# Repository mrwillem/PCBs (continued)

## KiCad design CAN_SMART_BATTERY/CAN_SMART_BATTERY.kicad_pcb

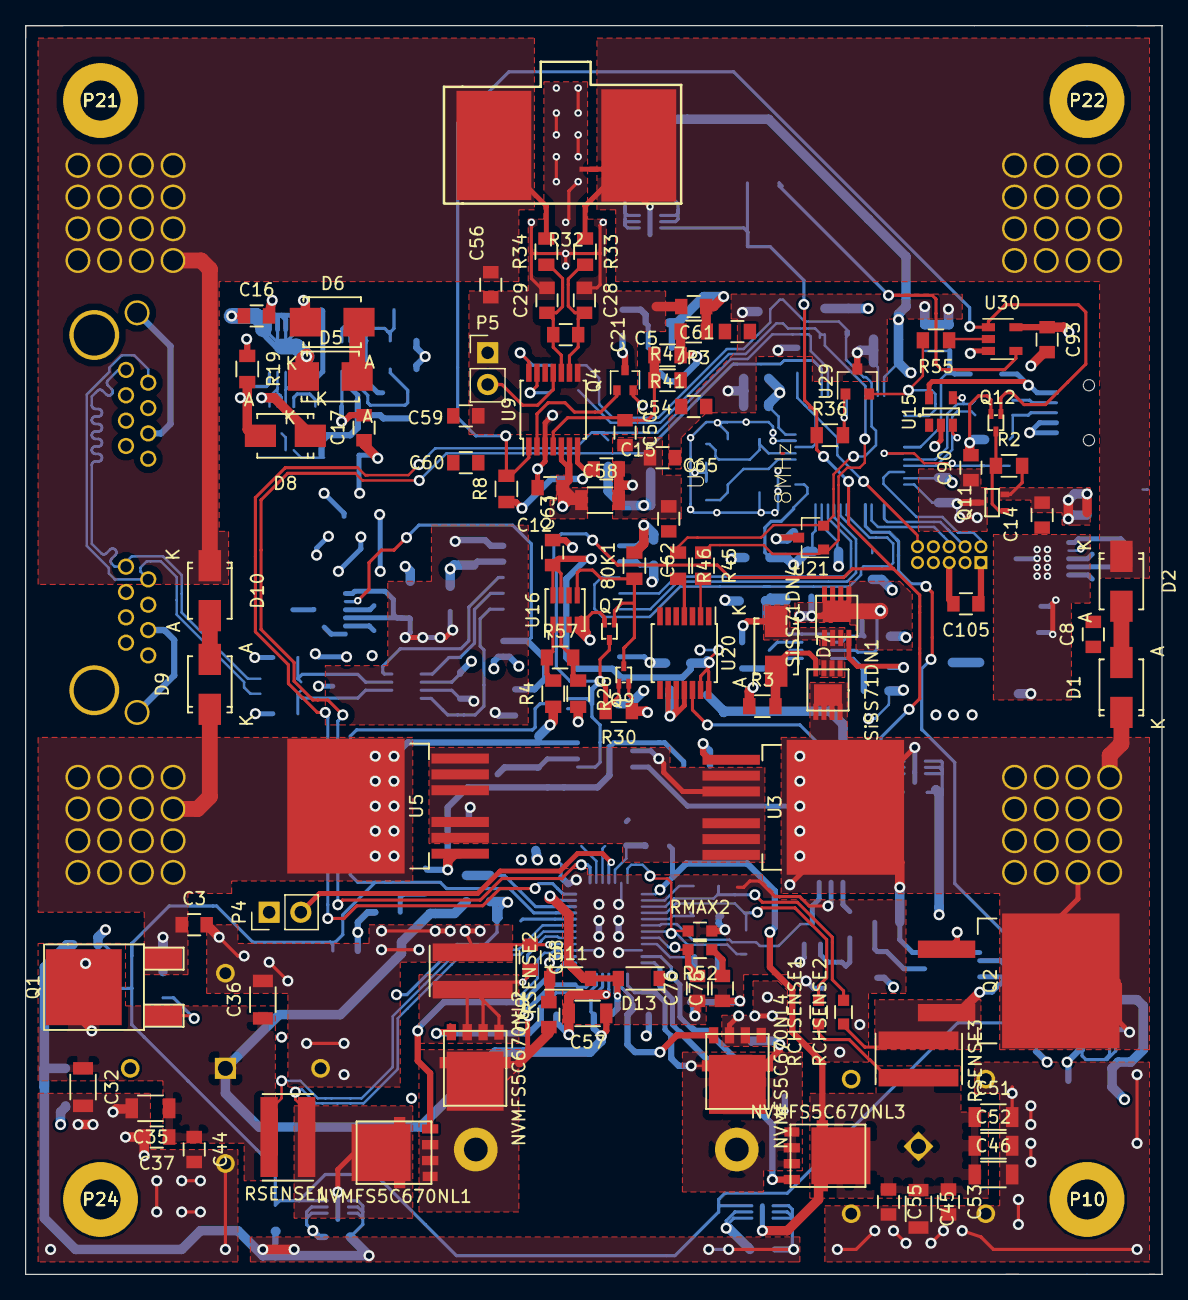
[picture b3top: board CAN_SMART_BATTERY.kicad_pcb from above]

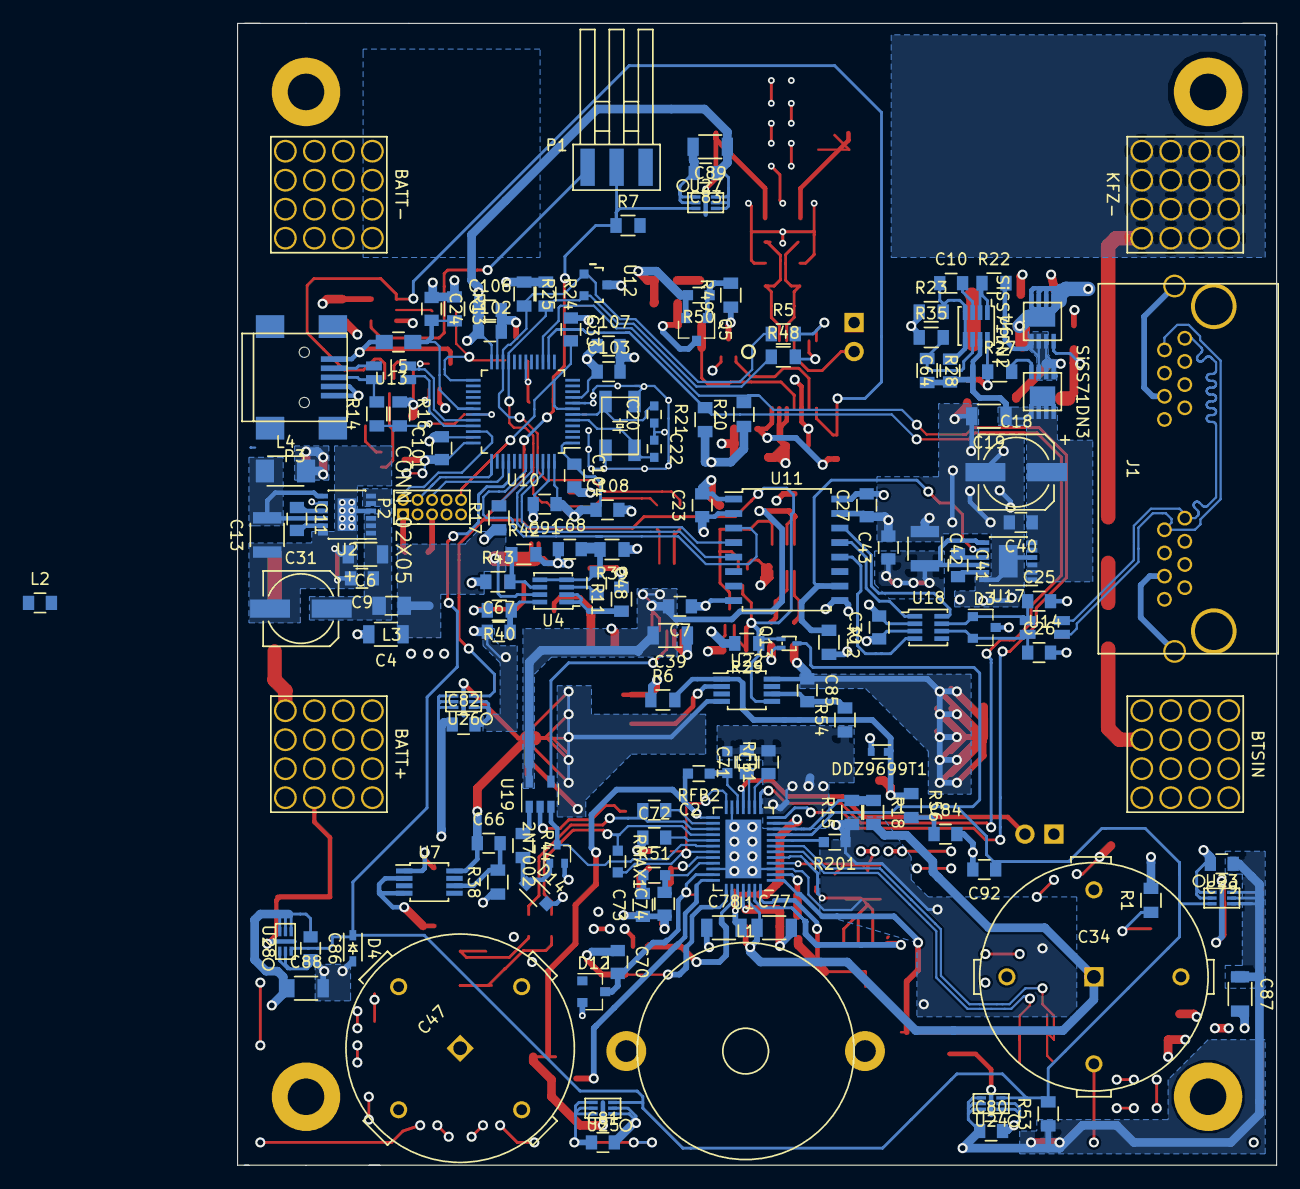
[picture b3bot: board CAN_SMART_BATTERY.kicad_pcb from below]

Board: 4 copper layers, 91.0 x 100.0 mm, 249 parts (144 on the bottom side), 134 nets.

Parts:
2N7002: Q_NMOS_GSD; SOT-323
80K1: R; R_0805_HandSolder
BATT+1: BATT+; WE_threaded_shank_M5_160A
BATT-1: BATT-; WE_threaded_shank_M5_160A
BTSIN1: BTSIN; WE_threaded_shank_M5_160A
C1, C64, C68: 470nF; C_0805
C2, C72: 100pF; C_0805
C3, C8: 100pF 150V; C_0805
C4, C6, C19, C32, C35, C36, C45, C46, C51, C52: 4.7uF GRM31CR71H47; C_1206
C5, C7, C9, C12, C21, C23, C24, C25, C26, C27, C28, C29, C30, C33, C37, C40, C44, C53, C54, C55, C56, C59, C60, C61, C62, C63, C65, C79, C80, C81, C82, C83, C86, C91, C93, C101, C102, C103, C104, C105: 100nF; C_0805
C10, C15, C48: 1uF; C_0805
C11, C41: 1uF 0805ZC105KAT2A; C_0805
C13, C42: 10uF; C_1210
C14, C43: 1uF GRM219R71E105KA88D; C_0805
C16: 100pF 60V; C_0805
C17, C67: 2nFC; C_0805
C18, C31: 33uF; c_elec_6.3x7.7
C20, C22: 22pF; C_0603
C34, C47: 56uF; Capacitors_PEH225MF_20mm
C38: 333nF; C_0805
C39, C57, C58, C78: 10uF; C_1206
C50: 3,3nF; C_0805
C66, C85: 47nF; C_0805
C69, C70, C73, C74, C75, C76: C; C_0805
C71: 220nF; C_0805
C77: 100nF; C_1206
C84, C92: 10nF; C_0805
C87, C88, C89: 4,7uF; C_1206
C90, C107: 4,7uF; C_0805
C106, C108: 2,2uF; C_0805
D1, D2, D7, D8, D9, D10: ZENER; SMA_Standard
D3: D_Schottky_x2_ACom_KKA; SOT-23
D4: ZENER; SOD-323-Handsoldering
D5, D6: ZENER; SMB_Standard
D11: D_Schottky; SOD-123
D12: D_Schottky_x2_KCom_AAK; SOT-23
D13: SBR0560S1; SOD-123
D14: ZENER; SOD-323_HandSoldering
DDZ9699T1: ZENER; SOD-523
J1: RJHSE-5380-02; RJHSE538X-02-noled
JP1: Jumper_NC_Small; NetTie-I_Connected_SMD
JP2: Jumper_NC_Small; NetTie0.4mmSMD
JP3: Jumper_NO_Small; R_0805_HandSolder
KFZ-1: KFZ-; WE_threaded_shank_M5_160A
L1: WE_7443641500; Choke_Toroid_horizontal_Diameter19mm_AIRD02_Abracon
L2: L_Small; C_0805
L3: 12 uH CV201210-180K; Choke_SMD_2016_Standard
L4: 100nHNLCV32-PFR1; Choke_SMD_3225_Standard
L5: INDUCTOR; C_0805_HandSoldering
NVMFS5C670NL1, NVMFS5C670NL2, NVMFS5C670NL3, NVMFS5C670NL4: NTMFS5C646NL; SO8FL_DFN5x6_pitch1.27
P1: CONN_01X03; SMD_PIN_HEADER_01x03_angled
P2: CONN_02X05; Pin_Header_Straight_2x05_Pitch1.27mm
P3: USB_B; USB_Mini-B
P4, P5: CONN_01X02; Pin_Header_Straight_1x02_Pitch2.54mm
P10: P10; hole
P21: P21; hole
P22: P22; hole
P24: P24; hole
Q1: ATP304-TL-H; TO-252-2Lead
Q2: Q_NMOS_GDS; TO-263-2Lead
Q4: 2N7002; SOT-323
Q5: BSS84; SOT-23
Q7, Q9, Q13: NTK3043NT1G; SOT-723
Q11: MTM231232LBF; SC-70
Q12: NTK3134NT1G; SOT-723
R1, R2, R3, R8, R19, R20, R21, R53: 100K; R_0805_HandSolder
R4: 6,7M; R_0805_HandSolder
R5, R33, R34, R36, R44, R45, R46, R48, R55: 100R; R_0805_HandSolder
R6, R27, R40: 10R; R_0805_HandSolder
R7, R15, R18: R; R_0805_HandSolder
R11, R22: 324K; R_0805_HandSolder
R12: 40K; R_0805_HandSolder
R13, R16: 47K; R_0805_HandSolder
R14: 1K5; R_0805_HandSolder
R17, R29, R56, R57: 10K; R_0805_HandSolder
R23, R39: 47K5; R_0805_HandSolder
R24, R25: 2K; R_0805_HandSolder
R26: 2700K; R_0805_HandSolder
R28, R42: 12K; R_0805_HandSolder
R30: 1M; R_0805_HandSolder
R32: 0.0002R; WSLP_5931_DALE
R35, R43: 365K; R_0805_HandSolder
R38, R54: 1K; R_0805_HandSolder
R41: 300K; R_0805_HandSolder
R47: 16K5; R_0805_HandSolder
R49: 169K; R_0805_HandSolder
R50, R201: 100K; R_0603_HandSolder
R51, R52: R; R_0603_HandSolder
RCHSENSE1, RCHSENSE2: 100R; R_0603_HandSolder
RFB1, RFB2: R; R_0603_HandSolder
RMAX1, RMAX2: R; R_0603_HandSolder
RSENSE1, RSENSE2, RSENSE3: 0.003RKRL6432; R_6432
SiSS71DN1, SiSS71DN2, SiSS71DN3, SiSS71DN4: SiSS71DN; PowerPack1212-8S_Pitch0.65mm
U1: LTC4020; QFN-38-1EP_5x7mm_Pitch0.5mm
U2, U17: LTC3245; MSOP-12-1EP_3x4mm_Pitch0.65mm
U3, U5: IPB180P04P4L-02; TO-263-7Lead
U4, U6: LTC4366-2; SOT23-8
U7: LTC4395; MSOP-8_3x3mm_Pitch0.65mm
U8: 8MHz; Xtal_Ceramic_5x3.2
U9: BQ34Z100-G1; TSSOP-14_4.4x5mm_Pitch0.65mm
U10: STM32L433CC; LQFP-48_7x7mm_Pitch0.5mm
U11: ADUM1301; SOIC-16W_7.5x10.3mm_Pitch1.27mm
U12, U21, U29: AZ23c5v6; SOT-23
U13, U14: USB-CMC-Wuerth; CMC-SMD-Wuerth
U15: TVS-ARRAY-SOT5; SOT-23-5
U16: LTC2960; SOT23-8
U18: TCAN330; SOT23-8
U19: LT6015; SOT-23-5
U20: MCP45HVX1; TSSOP-14_4.4x5mm_Pitch0.65mm
U22: LTC4359; MSOP-8_3x3mm_Pitch0.65mm
U23, U24, U25, U26, U27, U28: TMP302; SOT-563
U30: SN74AHC1G09; SOT-23-5

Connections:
3V3BQ: C12.1, C14.1, C58.1, L4.2, Q11.2, R2.2, U9.5, U9.6
3V3MCU: 80K1.2, C23.2, C79.1, C80.1, C81.1, C82.1, C83.1, C86.1, C87.1, C88.1, C89.1, C90.1, C91.1, C93.1, C101.1, C102.1, C103.1, C104.1, C105.1, C106.1, C107.1, C108.1, P2.1, Q11.3, R20.1, R21.1, R24.1, R25.1, R29.2, R53.1, U10.1, U10.9, U10.24, U10.36, U10.48, U11.1, U20.1, U23.4, U23.5, U23.6, U24.4, U24.5, U24.6, U25.4, U25.5, U25.6, U26.4, U26.5, U26.6, U27.4, U27.5, U27.6, U28.4, U28.5, U28.6, U30.5
+2V5: C15.1, R8.1, U9.7
ALARM: Q12.1, R8.2, U9.1, U30.1
BATSENSE: C50.1, R41.2, R47.1, U9.4
BATT+: BATT+1.1, C8.1, C66.1, D1.1, Q2.2, SiSS71DN1.5, SiSS71DN1.6, SiSS71DN1.7, SiSS71DN1.8, U3.4, U7.8, U22.4
BATT-: BATT-1.1, C8.2, D2.1, JP2.2, R32.1, R33.1
BG2: NVMFS5C670NL4.4, U1.33
CALVINSHIELD: C5.2, C12.2, C15.2, C28.1, C29.2, C50.2, C54.2, C56.2, C58.2, C59.2, C60.2, C61.2, C62.2, C65.2, JP2.1, P5.1, Q4.2, R47.2, U9.3, U9.8
CANPGOOD: R12.1, U11.10, U17.8
CANPREDIODE: D8.1, R22.2, SiSS71DN2.1, SiSS71DN2.2, SiSS71DN2.3, SiSS71DN3.1, SiSS71DN3.2, SiSS71DN3.3
CANRX: U10.45, U11.5
CANSHLD: J1.6, J1.14, J1.17
CANSLEEP: U10.43, U11.3
CANTX: U10.46, U11.4
CANVIN: C18.1, C19.1, C40.1, C64.1, R28.2, SiSS71DN3.5, SiSS71DN3.6, SiSS71DN3.7, SiSS71DN3.8, U6.7, U17.1, U17.2, U17.3, U17.5, U17.6
CANVOUT: C27.2, C30.1, C42.2, C43.1, R12.2, U11.16, U17.7, U17.10, U18.3
CSOUT: C72.2, U1.24
DISCONNECT: R14.1, R16.2, U10.31
ECANGND: C16.2, C17.1, C18.2, C19.2, C25.2, C26.2, C27.1, C30.2, C40.2, C42.1, C43.2, D3.3, D6.1, J1.3, J1.7, J1.11, J1.15, R19.1, R23.1, R35.1, U11.9, U11.15, U17.4, U17.12, U17.13, U18.2
ECANH: J1.1, J1.9, U14.1
ECANL: J1.2, J1.10, U14.4
ECANV+: C16.1, D5.1, J1.8, J1.16, SiSS71DN2.5, SiSS71DN2.6, SiSS71DN2.7, SiSS71DN2.8
EXTRESET: C33.1, P2.10, U10.7
GND: 2N7002.2, C1.2, C4.2, C6.2, C7.1, C9.2, C13.1, C14.2, C23.1, C24.1, C31.2, C33.2, C39.1, C62.1, C63.1, C67.1, C71.2, C72.1, C73.1, C74.1, C75.1, C76.1, C79.2, C80.2, C81.2, C82.2, C84.2, C86.2, C87.2, C88.2, C90.2, C91.2, C92.2, C93.2, C101.2, C102.2, C103.2, C104.2, C105.2, C106.2, C107.2, C108.2, D4.2, D14.2, JP1.1, L2.2, P2.3, P2.5, P2.7, P2.9, P3.4, P3.5, P4.1, Q7.2, Q9.2, Q12.2, Q13.2, R3.1, R13.1, R15.1, R16.1, R17.1, R26.2, R30.1, R39.1, R43.1, R54.1, R201.1, RFB1.1, RMAX2.2, U1.3, U1.18, U1.29, U1.39, U2.4, U2.12, U2.13, U10.8, U10.23, U10.35, U10.47, U11.2, U11.8, U12.3, U15.2, U16.4, U19.2, U20.3, U20.5, U20.9, U20.10, U20.11, U21.3, U23.1, U23.2, U24.1, U24.2, U25.1, U25.2, U26.1, U26.2, U28.1, U28.2, U29.3, U30.3
ILIM: 2N7002.3, U1.25, U19.3
INTVCC: C78.2, D11.2, D13.2, U1.11, U1.34
ITH: C76.2, R52.2, U1.27
KFZ-: C3.2, C32.2, C34.2, C35.2, C36.2, C37.2, C38.1, C44.2, C45.2, C46.2, C47.2, C51.2, C52.2, C53.2, C54.1, C55.2, C56.1, C57.2, C59.1, C60.1, C61.1, C65.1, C77.2, C78.1, C83.2, C89.2, D10.1, KFZ-1.1, NVMFS5C670NL4.1, NVMFS5C670NL4.2, NVMFS5C670NL4.3, R32.2, R34.2, R38.1, RSENSE2.1, U1.4, U1.35, U27.1, U27.2
MOSCONTROL: R55.1, U30.2
MOSDETECT: P1.2, Q7.3, Q9.1, Q13.1, R7.1, R29.1, R30.2, R36.1, U22.5, U26.3, U27.3
unnamed: 2N7002.1, D14.1, R44.2
unnamed: 80K1.1, Q7.1, Q9.3, U16.5
unnamed: C1.1, U1.14
unnamed: C2.1, RCHSENSE2.2, U1.22
unnamed: C2.2, U1.21
unnamed: C10.1, C64.2, R23.2, U6.4, U6.5
unnamed: C10.2, U6.3
unnamed: C11.1, U2.9
unnamed: C11.2, U2.11
unnamed: C17.2, R27.1, U6.8
unnamed: C20.2, U8.1, U10.6
unnamed: C21.1, C28.2, R33.2, U9.9
unnamed: C21.2, C29.1, R34.1, U9.10
unnamed: C22.2, U8.3, U10.5
unnamed: C25.1, D3.1, U14.2, U18.7
unnamed: C26.1, D3.2, U14.3, U18.6
unnamed: C41.1, U17.9
unnamed: C41.2, U17.11
unnamed: C48.1, C68.2, R39.2, U4.4, U4.5
unnamed: C48.2, U4.3
unnamed: C66.2, R38.2, U7.6
unnamed: C67.2, R40.1, U4.8
unnamed: C69.2, D11.1, U1.2
unnamed: C70.2, D12.3, D13.1, U1.30
unnamed: C71.1, U1.15
unnamed: C73.2, R51.1
unnamed: C75.2, R52.1
unnamed: C84.1, R56.2
unnamed: C85.2, R54.2, U22.6
unnamed: D1.2, D2.2
unnamed: D5.2, D6.2
unnamed: D7.2, R3.2, SiSS71DN1.4
unnamed: D8.2, R19.2, SiSS71DN2.4
unnamed: D9.2, D10.2
unnamed: DDZ9699T1.1, R6.2, R56.1, U5.1, U22.1
unnamed: JP3.2, Q5.3, R41.1
unnamed: NVMFS5C670NL1.4, U1.1
unnamed: NVMFS5C670NL2.4, U1.37
unnamed: P1.1, U30.4
unnamed: P3.2, U13.4
unnamed: P3.3, R14.2, U13.1
unnamed: P4.2, U1.16
unnamed: P5.2, U9.11
unnamed: Q1.1, R1.1
unnamed: Q2.1, U7.1
unnamed: Q4.3, R49.1
unnamed: Q5.1, R49.2, R50.1
unnamed: Q11.1, Q12.3, R2.1
unnamed: R4.2, R57.1, U16.1
unnamed: R5.2, U9.14
unnamed: R6.1, U3.1
unnamed: R11.1, U4.1, U4.2
unnamed: R15.2, R18.1, U1.10
unnamed: R17.2, U10.44
unnamed: R22.1, U6.1, U6.2
unnamed: R26.1, R57.2, U16.2
unnamed: R27.2, SiSS71DN3.4
unnamed: R28.1, R35.2, U6.6
unnamed: R36.2, U10.18, U29.1
unnamed: R40.2, SiSS71DN4.4
unnamed: R42.1, R43.2, U4.6
unnamed: R44.1, U19.1
unnamed: R45.2, U20.2
unnamed: R46.2, U20.4
unnamed: R48.2, U9.13
unnamed: R55.2, U10.25, U29.2
unnamed: R201.2, U1.8
unnamed: RCHSENSE1.2, RMAX1.1, U1.23
unnamed: RFB1.2, RFB2.1, U1.17
unnamed: RMAX1.2, RMAX2.1, U1.19, U1.26
unnamed: U11.12, U18.4
unnamed: U11.13, U18.1
unnamed: U11.14, U18.8
unnamed: U19.4, U20.12
OD_CHARGESTAT1: R20.2, U1.12, U10.15
OD_CHARGESTAT2: R21.2, U1.13, U10.14
PMOS_SOURCE: DDZ9699T1.2, U3.2, U3.3, U3.5, U3.6, U3.7, U5.2, U5.3, U5.5, U5.6, U5.7, U22.2
PREDIODE: C5.1, D7.1, JP3.1, Q5.2, R11.2, R50.2, SiSS71DN1.1, SiSS71DN1.2, SiSS71DN1.3, SiSS71DN4.1, SiSS71DN4.2, SiSS71DN4.3
SCL: R24.2, R45.1, R48.1, U10.21, U12.2, U21.1
SDA: R5.1, R25.2, R46.1, U10.22, U12.1, U21.2
SENSEBOT: C38.2, NVMFS5C670NL2.1, NVMFS5C670NL2.2, NVMFS5C670NL2.3, RSENSE2.2, U1.5
SENSE_ENABLE: Q4.1, U9.2
SHDN_LOAD: C92.1, D4.1, Q13.3, R53.2, U1.9, U10.40, U23.3, U24.3, U25.3, U28.3
SW1: C69.1, L1.2, NVMFS5C670NL1.1, NVMFS5C670NL1.2, NVMFS5C670NL1.3, NVMFS5C670NL2.5, NVMFS5C670NL2.6, NVMFS5C670NL2.7, NVMFS5C670NL2.8, U1.38
SW2: C70.1, D12.2, L1.1, NVMFS5C670NL3.1, NVMFS5C670NL3.2, NVMFS5C670NL3.3, NVMFS5C670NL4.5, NVMFS5C670NL4.6, NVMFS5C670NL4.7, NVMFS5C670NL4.8, U1.32
SWCLK: P2.4, U10.37
SWDIO: P2.2, U10.34
SWO: P2.6, U10.39
TG2: NVMFS5C670NL3.4, U1.31
USBCONNECTED: C24.2, L5.1, R13.2, U10.30
USBD+: U10.33, U13.2, U15.3
USBD-: U10.32, U13.3, U15.4
USBVCC: L5.2, P3.1, U15.5
VBAT_LTC4020: C45.1, C46.1, C47.1, C51.1, C52.1, C53.1, C55.1, NVMFS5C670NL3.5, NVMFS5C670NL3.6, NVMFS5C670NL3.7, NVMFS5C670NL3.8, RCHSENSE1.1, RFB2.2, RSENSE3.2, U1.20
VC: C74.2, R51.2, U1.28
VCCUNFILTERED: C13.2, L4.1, U2.7, U2.10
VCHARGEBATT: Q2.3, RCHSENSE2.1, RSENSE3.1, U7.2, U7.4
VIN: C6.1, C9.1, C31.1, L3.2, U2.1, U2.2, U2.3, U2.5, U2.6
VINR: NVMFS5C670NL1.5, NVMFS5C670NL1.6, NVMFS5C670NL1.7, NVMFS5C670NL1.8, RSENSE1.1, U1.6
VIN_LTC4020: C32.1, C34.1, C35.1, C36.1, C37.1, C44.1, C57.1, C77.1, Q1.2, R18.2, RSENSE1.2, U1.7, U1.36
VPROT: C4.1, C7.2, C39.2, C63.2, C68.1, L3.1, R42.2, SiSS71DN4.5, SiSS71DN4.6, SiSS71DN4.7, SiSS71DN4.8, U4.7, U16.7, U16.8, U19.5, U20.13, U20.14
VSYS: BTSIN1.1, C3.1, C85.1, D9.1, Q1.3, R1.2, R4.1, U5.4, U22.8
stmxtalgnd: C20.1, C22.1, JP1.2, U8.2, U8.4
